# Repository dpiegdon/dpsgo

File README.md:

<!-- vim: tw=72 fo+=a
-->

DPSGO
=====

David's Pretty Satisfactory Gps-disciplined Oscillator

GPS disciplined oscillator
==========================

Accurate frequency reference for measurement equipment.

A 10MHz OCXO is tuned to a timing signal of a GPS, e.g. the 1PPS output.
A frequency syntheziser then generates different signals from this
reference as needed/configured by the user.

Development status
------------------

Currently I am working on the firmware for V1 of the PCB. During that I
found multiple issues with PCB-V1 (<a
href="https://github.com/dpiegdon/dpsgo/blob/master/pcb/export/PCB-v1.pdf">Schematic</a>)
which hopefully culminate in another revision of the PCB, and then the
firmware. See <a
href="https://github.com/dpiegdon/dpsgo/blob/master/pcb/export/PCB-v1.ERRATA">PCB-V1
ERRATA</a>.

I.e.: usable, but only as a prototype development platform for V2.

The main control loop (OCXO -> frequency comparison -> DAC) works and
the OCXO can be tuned to the GPS signal within 1PPB or better.

The chosen *tiny* FPGA is too small to hold all the logic that was
designated for it. Most LEDs are connected to it and cannot be addressed
because of that. Currently also the rotary encoder and buttons are
connected to it and are usable, but may be removed to have more logic
for frequency adjustment. In PCB-V2 I will likely move the UI to the
microcontroller, or pick a slightly larger FPGA, e.g. the HX1K.

System components PCB-V1
------------------------

<a
href="https://github.com/dpiegdon/dpsgo/blob/master/pcb/export/PCB-v1.pdf">Schematic.</a>

OCXO: refurbished 8663-XS with 10MHz output

DAC: AD5761R 16bit high quality low speed DAC with internal reference,
generates tuning signal for OCXO

GPS: uBlox NEO 7M module with 1PPS output

VCXO: Si5351-C frequency generator for programmable output frequencies

 * CLK0: 90MHz as input for frequency comparison in the FPGA (for
   automatic tuning)

 * CLK1: 10MHz reference output signal

 * other programmable outputs (currently disabled)

FPGA: Lattice LP384: measures difference between the generated reference
output and the GPS reference signal. That information is used to
calculate the tuning voltage for the OCXO.

uC: nRF52840 as system- and display-controller

Power input: 14-16V

PMIC: TPS652510 PMIC generating three rails of:

 * 12V: OCXO

 * 3.3V: digital logic

 * 1.2V: FPGA core voltage

Additional LDO for:

 * 10V: DAC output rail (from 12V rail)

Temperature sensors: MCP9808 under OCXO and on bottom-side of PMIC (not
visible in photo).

User interface:

 * SSD1306

 * Rotary encoder and buttons (via FPGA)

 * LEDs (currently not addressalbe as FPGA cannot hold more logic)

Interfaces:

 * USB to both GPS receiver and microcontroller

 * potentially Bluetooth or 802.11.5 to microcontroller

 * JTAG/SWD to microcontroller

External references
-------------------

A list of some hobby GPSDO designs:
https://attila.kinali.ch/blog/2016/02/07/gps-disciplined-oscillator

A GPSDO with rubidium standard:
http://www.medpants.com/my-reeds/itemlist/category/28-electronics

Alternative OCXO tuning schematic:
https://gerrysweeney.com/wp-content/uploads/2013/10/OCXO-Rev-1F.png

"bt7tbl" GPSDO that can be bought on the internets:
https://www.eevblog.com/forum/testgear/bg7tbl-gpsdo-master-reference/

Single-chip GPSDO control loop GPSDO:
https://www.analog.com/media/en/technical-documentation/application-notes/AN-1002.pdf

"OpenPPS" GPSDO project:
http://www.rocketmanrc.com/openpps.html

"Themis" GPSDO from HPSDR:
http://openhpsdr.org/wiki/index.php?title=GPSTCXO

GPSDO by dfannin:
https://github.com/dfannin/gpsdo

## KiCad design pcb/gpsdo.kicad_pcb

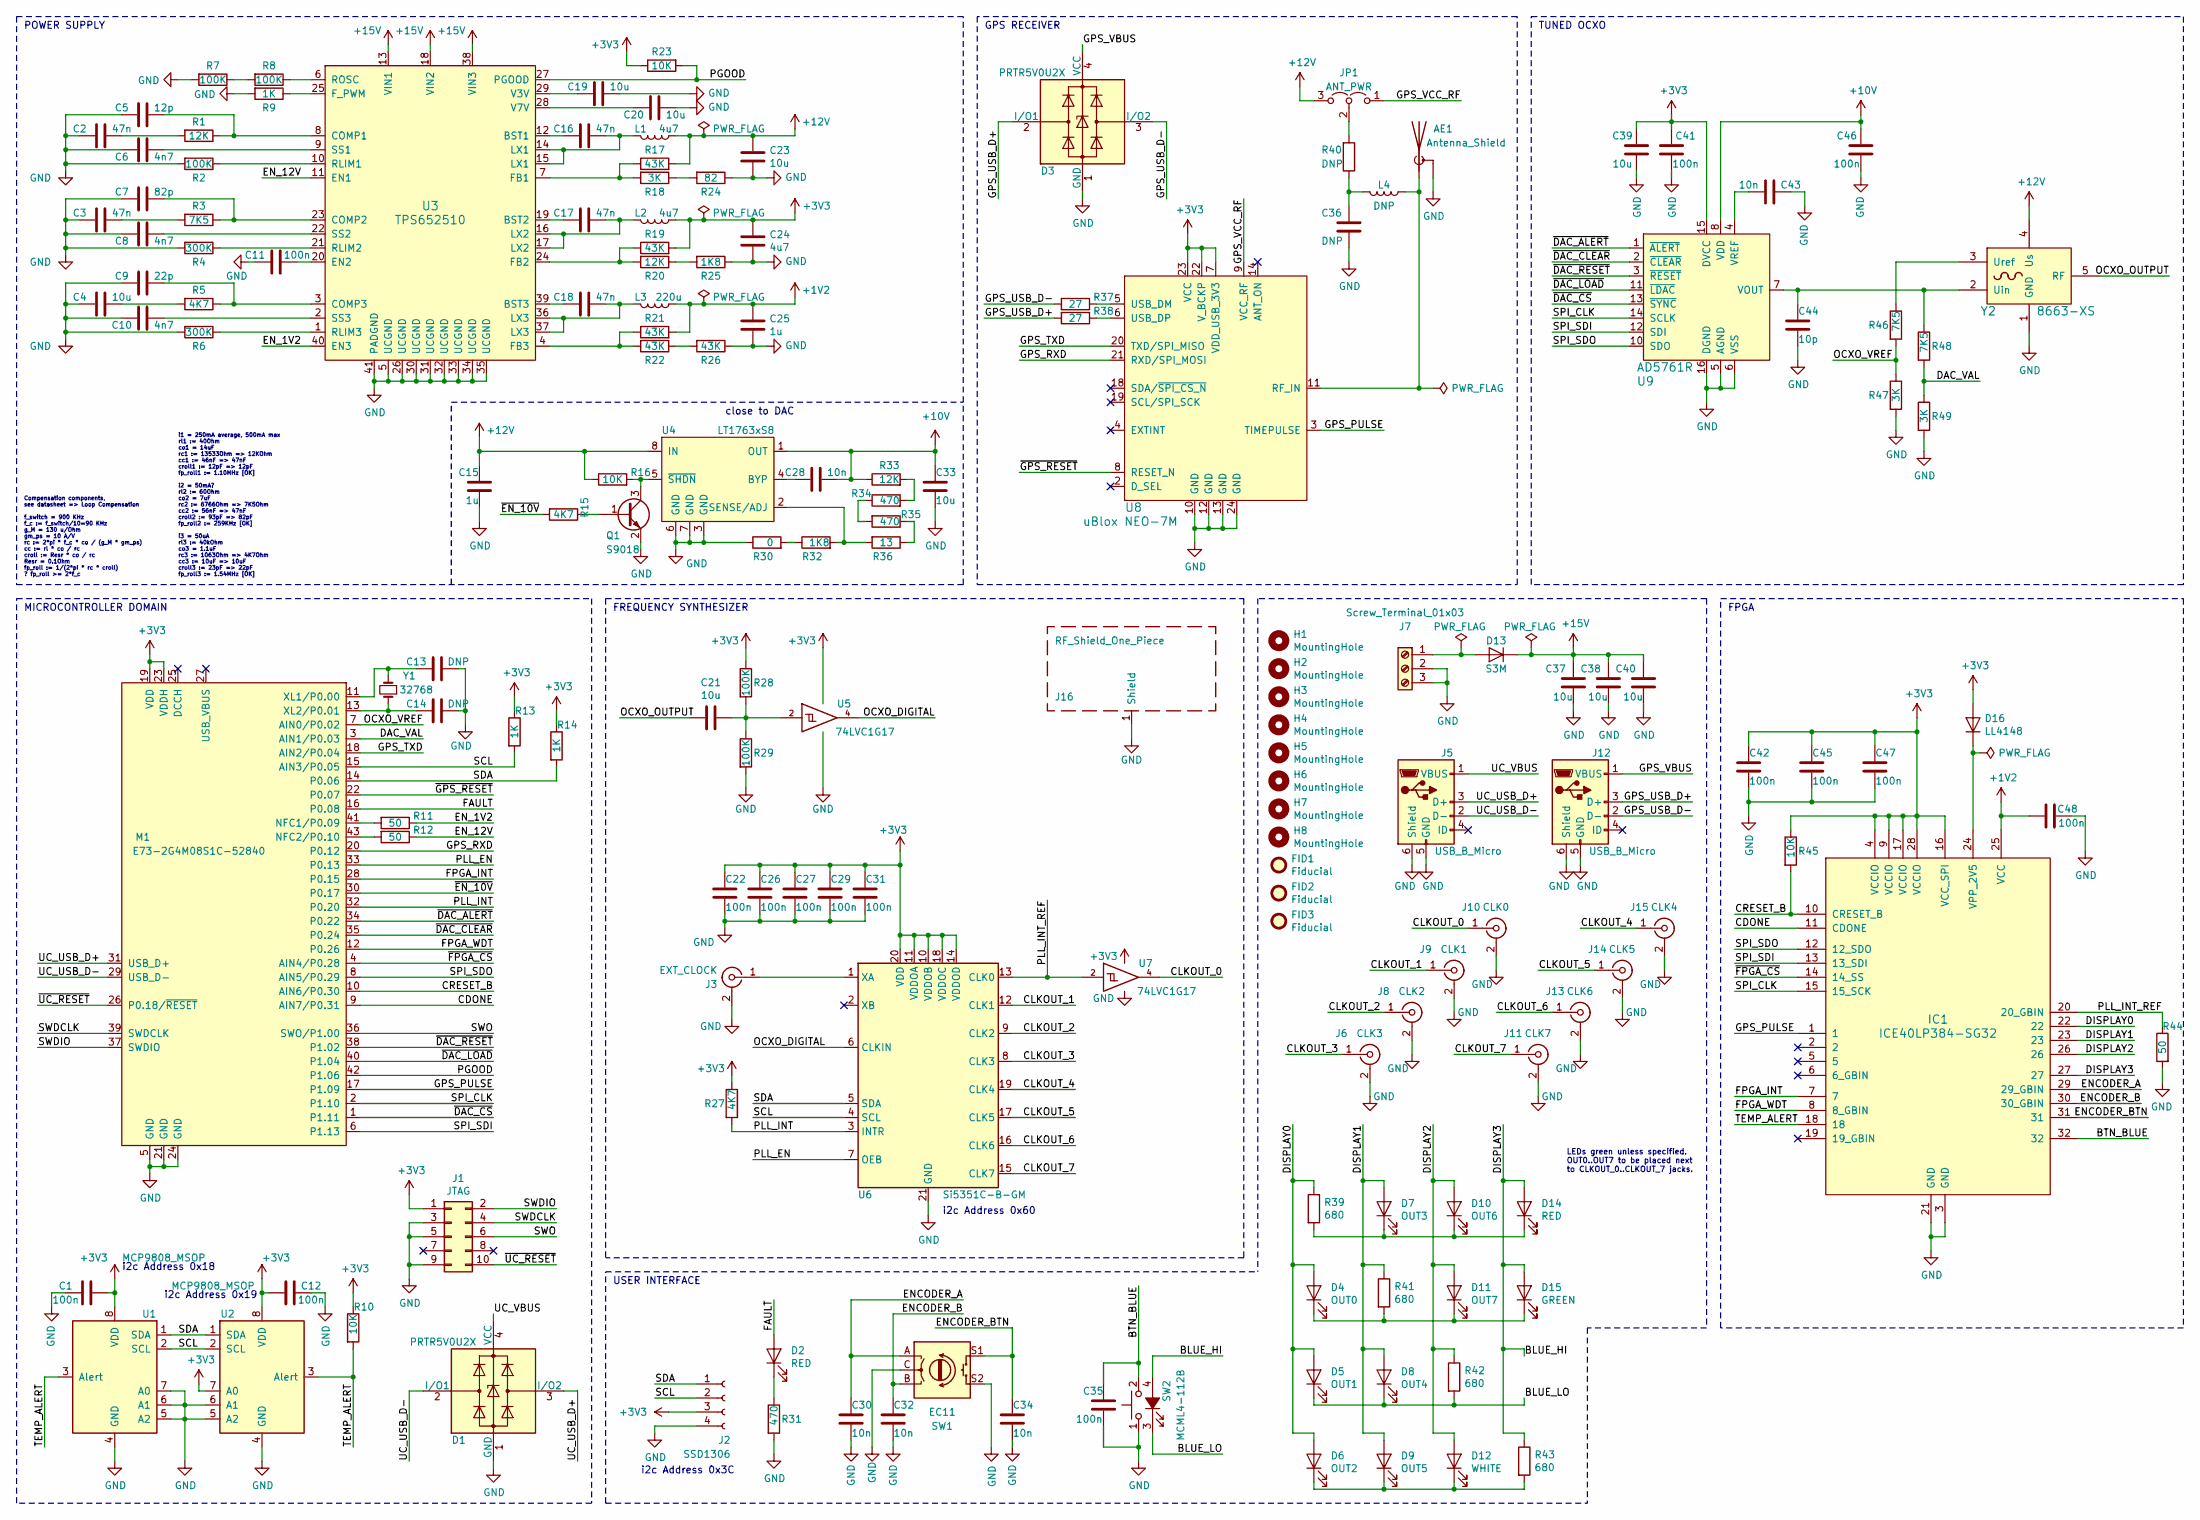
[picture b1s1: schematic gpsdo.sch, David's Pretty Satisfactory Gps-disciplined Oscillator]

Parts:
AE1: Antenna_Shield; Antenna-GPS-1575R
C1, C11, C12, C22, C26, C27, C29, C31, C35, C41, C42, C45, C46, C47, C48: 100n; C_0402_1005Metric
C2, C3, C16, C17, C18: 47n; C_0402_1005Metric
C4: 10u; C_0402_1005Metric
C5: 12p; C_0402_1005Metric
C6, C8, C10: 4n7; C_0402_1005Metric
C7: 82p; C_0402_1005Metric
C9: 22p; C_0402_1005Metric
C13, C14, C36: DNP; C_0402_1005Metric
C15, C25: 1u; C_0603_1608Metric
C19, C20, C33, C39: 10u; C_0603_1608Metric
C21, C23, C37, C38, C40: 10u; C_1210_3225Metric
C24: 4u7; C_0603_1608Metric
C28, C30, C32, C34, C43: 10n; C_0402_1005Metric
C44: 10p; C_0402_1005Metric
D1, D3: PRTR5V0U2X; SOT-143
D2: RED; D_1206_3216Metric
D4: OUT0; D_0603_1608Metric
D5: OUT1; D_0603_1608Metric
D6: OUT2; D_0603_1608Metric
D7: OUT3; D_0603_1608Metric
D8: OUT4; D_0603_1608Metric
D9: OUT5; D_0603_1608Metric
D10: OUT6; D_0603_1608Metric
D11: OUT7; D_0603_1608Metric
D12: WHITE; D_0603_1608Metric
D13: S3M; D_2010_5025Metric
D14: RED; D_0603_1608Metric
D15: GREEN; D_0603_1608Metric
D16: LL4148; D_MiniMELF
FID1, FID2, FID3: Fiducial; Fiducial_1mm_Mask3mm
H1, H2, H3, H4, H5, H6, H7, H8: MountingHole; MountingHole_4.3mm_M4_ISO14580_Pad
IC1: ICE40LP384-SG32; QFN-32-1EP_5x5mm_P0.5mm_EP3.6x3.6mm
J1: JTAG; PinHeader_2x05_P1.27mm_Vertical_SMD
J2: SSD1306; PinHeader_1x04_P2.54mm_Vertical
J3: EXT_CLOCK; U.FL_Molex_MCRF_73412-0110_Vertical
J5, J12: USB_B_Micro; USB_Micro-B_Aliexpress_7.2mm_Pitch
J6: CLK3; SMA_Molex_73251-1153_EdgeMount_Horizontal
J7: Screw_Terminal_01x03; TerminalBlock_Phoenix_PT-1,5-3-5.0-H_1x03_P5.00mm_Horizontal
J8: CLK2; SMA_Molex_73251-1153_EdgeMount_Horizontal
J9: CLK1; SMA_Molex_73251-1153_EdgeMount_Horizontal
J10: CLK0; SMA_Molex_73251-1153_EdgeMount_Horizontal
J11: CLK7; SMA_Molex_73251-1153_EdgeMount_Horizontal
J13: CLK6; SMA_Molex_73251-1153_EdgeMount_Horizontal
J14: CLK5; SMA_Molex_73251-1153_EdgeMount_Horizontal
J15: CLK4; SMA_Molex_73251-1153_EdgeMount_Horizontal
J16: RF_Shield_One_Piece; Laird_Technologies_BMI-S-202-F_16.50x16.50mm
JP1: ANT_PWR; SolderJumper-3_P1.3mm_Open_RoundedPad1.0x1.5mm
L1, L2: 4u7; L_7.3x7.3_H4.5
L3: 220u; L_Vishay_IHLP-1616
L4: DNP; L_0805_2012Metric
M1: E73-2G4M08S1C-52840; E73-2G4M80S1C
Q1: S9018; SOT-23
R1, R20: 12K; R_0402_1005Metric
R2, R7, R8, R28, R29: 100K; R_0402_1005Metric
R3: 7K5; R_0402_1005Metric
R4, R6: 300K; R_0402_1005Metric
R5, R27: 4K7; R_0402_1005Metric
R9, R13, R14: 1K; R_0402_1005Metric
R10, R23, R45: 10K; R_0402_1005Metric
R11, R12, R44: 50; R_0402_1005Metric
R15: 4K7; R_0603_1608Metric
R16: 10K; R_0603_1608Metric
R17: 43K; R_0603_1608Metric
R18, R47, R49: 3K; R_0603_1608Metric
R19, R21, R22, R26: 43K; R_0402_1005Metric
R24: 82; R_0603_1608Metric
R25: 1K8; R_0402_1005Metric
R30: 0; R_0603_1608Metric
R31: 470; R_0402_1005Metric
R32: 1K8; R_0603_1608Metric
R33: 12K; R_0603_1608Metric
R34, R35: 470; R_0603_1608Metric
R36: 13; R_0603_1608Metric
R37, R38: 27; R_0402_1005Metric
R39, R41, R42, R43: 680; R_0402_1005Metric
R40: DNP; R_0402_1005Metric
R46, R48: 7K5; R_0603_1608Metric
SW1: EC11; RotaryEncoder_Alps_EC11E-Switch_Vertical_H20mm
SW2: MCML4-112B; MCML4-L
U1, U2: MCP9808_MSOP; MSOP-8_3x3mm_P0.65mm
U3: TPS652510; QFN-40-1EP_6x6mm_P0.5mm_EP4.6x4.6mm_ThermalVias
U4: LT1763xS8; SO-8_3.9x4.9mm_P1.27mm
U5, U7: 74LVC1G17; SOT-23-5
U6: Si5351C-B-GM; QFN-20-1EP_4x4mm_P0.5mm_EP2.7x2.7mm
U8: uBlox NEO-7M; ublox_NEO_fixed_23
U9: AD5761R; TSSOP-16_4.4x5mm_P0.65mm
Y1: 32768; Crystal_SMD_3215-2Pin_3.2x1.5mm
Y2: 8663-XS; OCXO-8662-8663

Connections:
+1V2: C25.1, C48.1, IC1.25 (VCC), L3.1, R21.2
+3V3: C1.2, C12.2, C22.1, C24.1, C26.1, C27.1, C29.1, C31.1, C39.2, C41.2, C42.1, C45.1, C47.1, D16.2 (A), IC1.4 (VCCIO), IC1.9 (VCCIO), IC1.16 (VCC_SPI), IC1.17 (VCCIO), IC1.28 (VCCIO), J1.1, J2.3, L2.1, M1.19 (VDD), M1.23 (VDDH), R10.1, R13.1, R14.1, R19.2, R23.1, R27.1, R28.1, R45.1, U1.8 (VDD), U2.7 (A0), U2.8 (VDD), U5.5 (VCC), U6.10 (VDDOB), U6.11 (VDDOA), U6.14 (VDDOD), U6.18 (VDDOC), U6.20 (VDD), U7.5 (VCC), U8.7 (VDD_USB_3V3), U8.22 (V_BCKP), U8.23 (VCC), U9.15 (DVCC)
+10V: C28.2, C33.1, C46.2, R33.1, U4.1 (OUT), U9.8 (VDD)
+12V: C15.2, C23.1, JP1.3 (B), L1.1, R16.1, R17.2, U4.8 (IN), Y2.4 (Us)
+15V: C37.2, C38.2, C40.2, D13.1 (K), U3.13 (VIN1), U3.18 (VIN2), U3.38 (VIN3)
/BLUE_HI: D14.2 (A), D15.2 (A), IC1.27, R43.1, SW2.4 (A)
/BLUE_LO: D5.1 (K), D8.1 (K), R42.2, SW2.3 (K)
/BTN_BLUE: C35.1, IC1.32, SW2.2
/CDONE: IC1.11 (CDONE), M1.9 (AIN7/P0.31)
/CLKOUT_0: J10.1 (In), U7.4
/CLKOUT_1: J9.1 (In), U6.12 (CLK1)
/CLKOUT_2: J8.1 (In), U6.9 (CLK2)
/CLKOUT_3: J6.1 (In), U6.8 (CLK3)
/CLKOUT_4: J15.1 (In), U6.19 (CLK4)
/CLKOUT_5: J14.1 (In), U6.17 (CLK5)
/CLKOUT_6: J13.1 (In), U6.16 (CLK6)
/CLKOUT_7: J11.1 (In), U6.15 (CLK7)
/CRESET_B: IC1.10 (CRESET_B), M1.10 (AIN6/P0.30), R45.2
/DAC_VAL: M1.3 (AIN1/P0.03), R48.2, R49.1
/DISPLAY0: D4.2 (A), D5.2 (A), D6.2 (A), IC1.22, R39.1
/DISPLAY1: D7.2 (A), D8.2 (A), D9.2 (A), IC1.23, R41.1
/DISPLAY2: D10.2 (A), D11.2 (A), D12.2 (A), IC1.26, R42.1
/ENCODER_A: C30.1, IC1.29 (29_GBIN), SW1.A
/ENCODER_B: C32.1, IC1.30 (30_GBIN), SW1.B
/ENCODER_BTN: C34.1, IC1.31, SW1.S1
/EN_1V2: R11.1, U3.40 (EN3)
/EN_12V: R12.1, U3.11 (EN1)
/FAULT: D2.2 (A), M1.16 (P0.08)
/FPGA_INT: IC1.7, M1.28 (P0.15)
/FPGA_WDT: IC1.8 (8_GBIN), M1.12 (P0.26)
/GPS_PULSE: IC1.1, M1.17 (P1.09), U8.3 (TIMEPULSE)
/GPS_RXD: M1.20 (P0.12), U8.21 (RXD/SPI_MOSI)
/GPS_TXD: M1.18 (AIN2/P0.04), U8.20 (TXD/SPI_MISO)
/GPS_USB_D+: D3.2 (I/O1), J12.3 (D+), R38.2
/GPS_USB_D-: D3.3 (I/O2), J12.2 (D-), R37.2
/GPS_VBUS: D3.4 (VCC), J12.1 (VBUS)
/GPS_VCC_RF: JP1.1 (A), U8.9 (VCC_RF)
/OCXO_DIGITAL: U5.4, U6.6 (CLKIN)
/OCXO_OUTPUT: C21.2, Y2.5 (RF)
/OCXO_VREF: M1.7 (AIN0/P0.02), R46.2, R47.1
/PGOOD: M1.42 (P1.06), R23.2, U3.27 (PGOOD)
/PLL_EN: M1.33 (P0.13), U6.7 (OEB)
/PLL_INT: M1.32 (P0.20), R27.2, U6.3 (INTR)
/PLL_INT_REF: IC1.20 (20_GBIN), R44.1, U6.13 (CLK0), U7.2
/SCL: J2.2, M1.15 (AIN3/P0.05), R13.2, U1.2 (SCL), U2.2 (SCL), U6.4 (SCL)
/SDA: J2.1, M1.14 (P0.06), R14.2, U1.1 (SDA), U2.1 (SDA), U6.5 (SDA)
/SPI_CLK: IC1.15 (15_SCK), M1.2 (P1.10), U9.14 (SCLK)
/SPI_SDI: IC1.13 (13_SDI), M1.6 (P1.13), U9.12 (SDI)
/SPI_SDO: IC1.12 (12_SDO), M1.8 (AIN5/P0.29), U9.10 (SDO)
/SWDCLK: J1.4, M1.39 (SWDCLK)
/SWDIO: J1.2, M1.37 (SWDIO)
/SWO: J1.6, M1.36 (SWO/P1.00)
/TEMP_ALERT: IC1.18, R10.2, U1.3 (Alert), U2.3 (Alert)
/UC_USB_D+: D1.3 (I/O2), J5.3 (D+), M1.31 (USB_D+)
/UC_USB_D-: D1.2 (I/O1), J5.2 (D-), M1.29 (USB_D-)
/UC_VBUS: D1.4 (VCC), J5.1 (VBUS)
/~DAC_ALERT: M1.34 (P0.22), U9.1 (~ALERT)
/~DAC_CLEAR: M1.35 (P0.24), U9.2 (~CLEAR)
/~DAC_CS: M1.1 (P1.11), U9.13 (~SYNC)
/~DAC_LOAD: M1.40 (P1.04), U9.11 (~LDAC)
/~DAC_RESET: M1.38 (P1.02), U9.3 (~RESET)
/~EN_10V: M1.30 (P0.17), R15.2
/~FPGA_CS: IC1.14 (14_SS), M1.4 (AIN4/P0.28)
/~GPS_RESET: M1.22 (P0.07), U8.8 (RESET_N)
/~UC_RESET: J1.10, M1.26 (P0.18/~RESET)
GND: AE1.2 (Shield), C1.1, C2.2, C3.2, C4.2, C5.1, C6.1, C7.1, C8.1, C9.1, C10.1, C11.1, C12.1, C13.1, C14.1, C15.1, C19.1, C20.1, C22.2, C23.2, C24.2, C25.2, C26.2, C27.2, C29.2, C30.2, C31.2, C32.2, C33.2, C34.2, C35.2, C36.2, C37.1, C38.1, C39.1, C40.1, C41.1, C42.2, C43.2, C44.2, C45.2, C46.1, C47.2, C48.2, D1.1 (GND), D3.1 (GND), IC1.3 (GND), IC1.21 (GND), J1.3, J1.5, J1.9, J2.4, J3.2 (Ext), J5.5 (GND), J5.6 (Shield), J6.2 (Ext), J7.2, J7.3, J8.2 (Ext), J9.2 (Ext), J10.2 (Ext), J11.2 (Ext), J12.5 (GND), J12.6 (Shield), J13.2 (Ext), J14.2 (Ext), J15.2 (Ext), J16.1, M1.5 (GND), M1.21 (GND), M1.24 (GND), Q1.2 (E), R2.2, R4.2, R6.2, R7.2, R9.2, R24.1, R25.1, R26.1, R29.2, R30.1, R31.2, R44.2, R47.2, R49.2, SW1.C, SW1.S2, SW2.1, U1.4 (GND), U1.5 (A2), U1.6 (A1), U1.7 (A0), U2.4 (GND), U2.5 (A2), U2.6 (A1), U3.5 (UCGND), U3.26 (UCGND), U3.30 (UCGND), U3.31 (UCGND), U3.32 (UCGND), U3.33 (UCGND), U3.34 (UCGND), U3.35 (UCGND), U3.41 (PADGND), U4.3 (GND), U4.6 (GND), U4.7 (GND), U5.3 (GND), U6.21 (GND), U7.3 (GND), U8.10 (GND), U8.12 (GND), U8.13 (GND), U8.24 (GND), U9.5 (AGND), U9.6 (VSS), U9.16 (DGND), Y2.1 (GND)
unnamed: AE1.1 (A), L4.1, U8.11 (RF_IN)
unnamed: C2.1, R1.2
unnamed: C3.1, R3.2
unnamed: C4.1, R5.2
unnamed: C5.2, R1.1, U3.8 (COMP1)
unnamed: C6.2, U3.9 (SS1)
unnamed: C7.2, R3.1, U3.23 (COMP2)
unnamed: C8.2, U3.22 (SS2)
unnamed: C9.2, R5.1, U3.3 (COMP3)
unnamed: C10.2, U3.2 (SS3)
unnamed: C11.2, U3.20 (EN2)
unnamed: C13.2, M1.11 (XL1/P0.00), Y1.2
unnamed: C14.2, M1.13 (XL2/P0.01), Y1.1
unnamed: C16.1, L1.2, U3.14 (LX1), U3.15 (LX1)
unnamed: C16.2, U3.12 (BST1)
unnamed: C17.1, L2.2, U3.16 (LX2), U3.17 (LX2)
unnamed: C17.2, U3.19 (BST2)
unnamed: C18.1, L3.2, U3.36 (LX3), U3.37 (LX3)
unnamed: C18.2, U3.39 (BST3)
unnamed: C19.2, U3.29 (V3V)
unnamed: C20.2, U3.28 (V7V)
unnamed: C21.1, R28.2, R29.1, U5.2
unnamed: C28.1, U4.4 (BYP)
unnamed: C36.1, L4.2, R40.1
unnamed: C43.1, U9.4 (VREF)
unnamed: C44.1, R48.1, U9.7 (VOUT), Y2.2 (Uin)
unnamed: D2.1 (K), R31.1
unnamed: D7.1 (K), D10.1 (K), D14.1 (K), R39.2
unnamed: D4.1 (K), D11.1 (K), D15.1 (K), R41.2
unnamed: D6.1 (K), D9.1 (K), D12.1 (K), R43.2
unnamed: D13.2 (A), J7.1
unnamed: D16.1 (K), IC1.24 (VPP_2V5)
unnamed: J3.1 (In), U6.1 (XA)
unnamed: JP1.2 (C), R40.2
unnamed: M1.41 (NFC1/P0.09), R11.2
unnamed: M1.43 (NFC2/P0.10), R12.2
unnamed: Q1.1 (B), R15.1
unnamed: Q1.3 (C), R16.2, U4.5 (~SHDN)
unnamed: R2.1, U3.10 (RLIM1)
unnamed: R4.1, U3.21 (RLIM2)
unnamed: R6.1, U3.1 (RLIM3)
unnamed: R7.1, R8.2
unnamed: R8.1, U3.6 (ROSC)
unnamed: R9.1, U3.25 (F_PWM)
unnamed: R17.1, R18.2, U3.7 (FB1)
unnamed: R18.1, R24.2
unnamed: R19.1, R20.2, U3.24 (FB2)
unnamed: R20.1, R25.2
unnamed: R21.1, R22.2, U3.4 (FB3)
unnamed: R22.1, R26.2
unnamed: R30.2, R32.1
unnamed: R32.2, R36.2, U4.2 (SENSE/ADJ)
unnamed: R33.2, R34.2
unnamed: R34.1, R35.2
unnamed: R35.1, R36.1
unnamed: R37.1, U8.5 (USB_DM)
unnamed: R38.1, U8.6 (USB_DP)
unnamed: R46.1, Y2.3 (Uref)

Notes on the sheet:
POWER SUPPLY
GPS RECEIVER
MICROCONTROLLER DOMAIN
TUNED OCXO
FREQUENCY SYNTHESIZER
FPGA
USER INTERFACE
close to DAC
i1 = 250mA average, 500mA max rl1 := 40Ohm co1 = 14uF rc1 := 13533Ohm => 12KOhm cc1 := 46nF => 47nF croll1 := 12pF => 12pF fp_roll1 := 1.10MHz [OK] i2 = 50mA? rl2 := 60Ohm co2 = 7uF rc2 := 6766Ohm => 7K5Ohm cc2 := 56nF => 47nF croll2 := 93pF => 82pF fp_roll2 := 259KHz [OK] i3 = 50uA rl3 := 40kOhm c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
Compensation components, see datasheet => Loop Compensation f_switch = 900 KHz f_c := f_switch/10=90 KHz g_M = 130 u/Ohm gm_ps = 10 A/V rc := 2*pi * f_c * co / (g_M * gm_ps) cc := rl * co / rc croll := Resr * co / rc Resr = 0.1Ohm fp_roll := 1/(2*pi * rc * croll) ? fp_roll >= 2*f_c
LEDs green unless specified. OUT0..OUT7 to be placed next to CLKOUT_0..CLKOUT_7 jacks.
i2c Address 0x19
i2c Address 0x3C
i2c Address 0x60
i2c Address 0x18

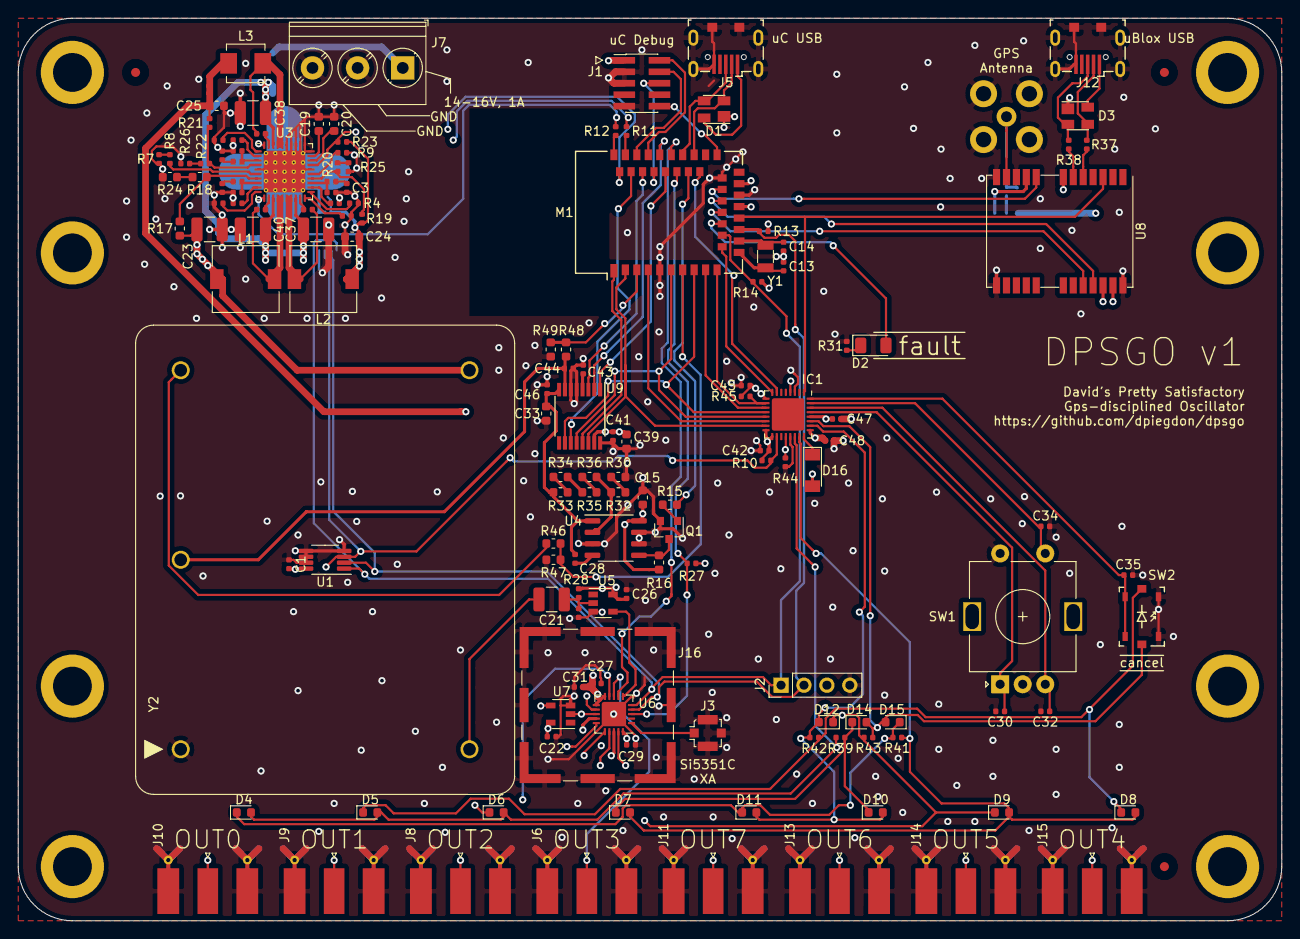
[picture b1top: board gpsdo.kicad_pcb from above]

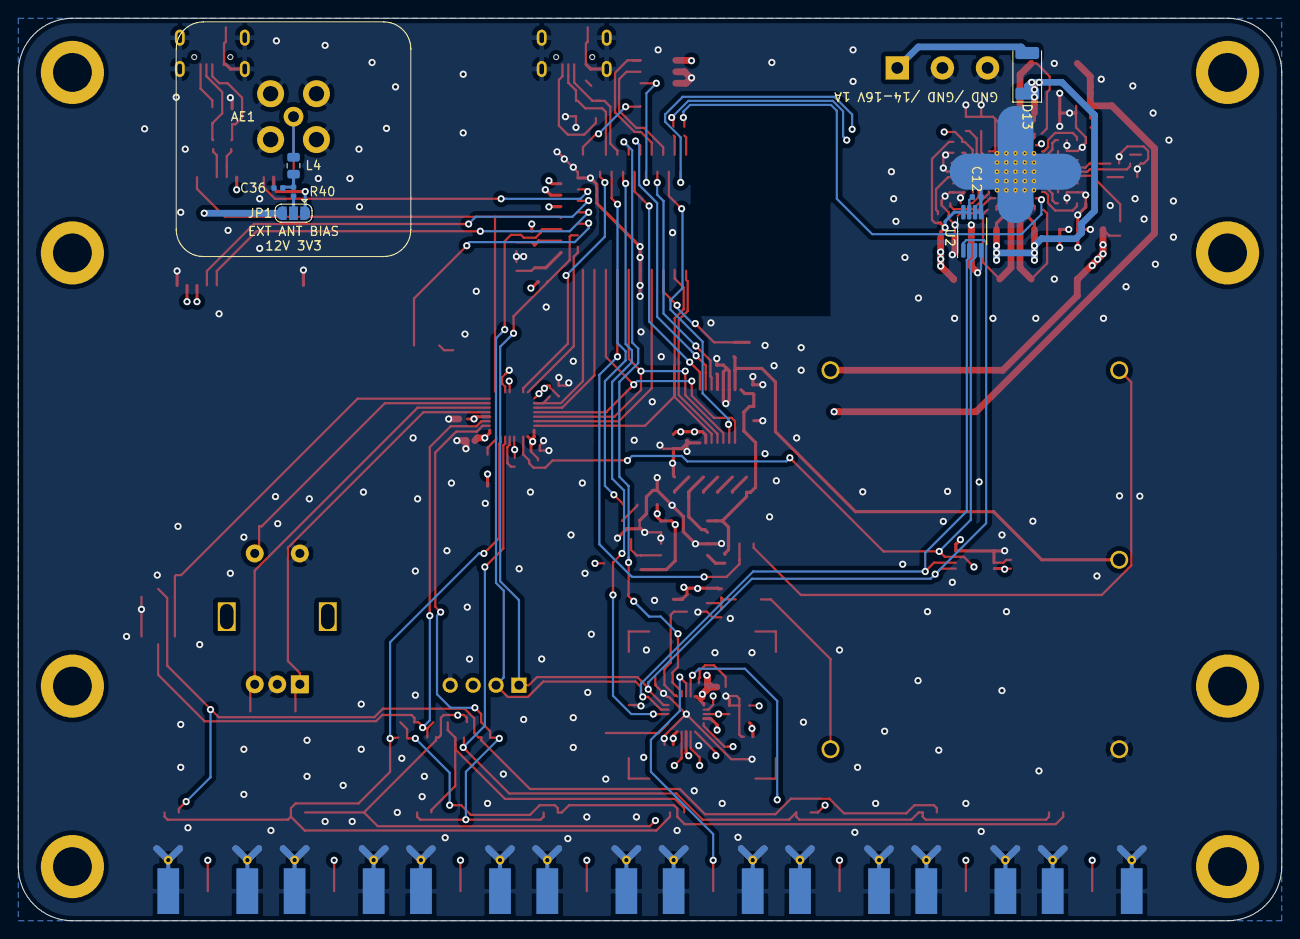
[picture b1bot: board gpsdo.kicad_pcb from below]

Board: 4 copper layers, 140.0 x 100.0 mm, 161 parts (8 on the bottom side), 124 nets.

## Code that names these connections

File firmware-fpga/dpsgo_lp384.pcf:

# SPI interface
set_io --warn-no-port SCK 15
set_io --warn-no-port SS 14
set_io --warn-no-port SDI 13
set_io --warn-no-port SDO 12
set_io --warn-no-port FPGA_INT 7
set_io --warn-no-port FPGA_WDT 8

# clocks
set_io --warn-no-port MAJOR_CLOCK 20
set_io --warn-no-port MINOR_CLOCK 1

# other IO
set_io --warn-no-port TEMP_ALERT 18

# buttons and encoder
set_io --warn-no-port ENCODER_A 29
set_io --warn-no-port ENCODER_B 30
set_io --warn-no-port ENCODER_BTN 31
set_io --warn-no-port BTN_BLUE 32

# LED matrix
set_io --warn-no-port LED_MATRIX[0] 22
set_io --warn-no-port LED_MATRIX[1] 23
set_io --warn-no-port LED_MATRIX[2] 26
set_io --warn-no-port LED_MATRIX[3] 27

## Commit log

2020-04-05 ignore temporary/intermediate files
2020-04-05 stub PCB files
2020-04-05 add submodules
2020-04-05 concept PCB
2020-04-05 description / concept
2020-04-05 add 8663-XS OCXO
2020-04-05 add ublox NEO-7 GPS module
2020-04-05 schematic progress, mark areas with TODOs
2020-04-06 add TPS652510, schematic progress and layout
2020-04-06 PCB progress
2020-04-06 schematic progress
2020-04-08 UI: rotary encoder would be nice, cleanup
2020-04-08 remove some errors and warnings
2020-04-08 project name: DPSGO; update README
2020-04-09 power concepts; bias and digitze OCXO output
2020-04-10 power progress, cleanup
2020-04-10 LEDs, front/rear panel
2020-04-11 stub verilog implementation to see how much logic fits into the LP384 ; schematic adaptions for that
2020-04-11 FPGA progress, interface and schematic-cleanup
2020-04-11 partial footprint assignment
2020-04-12 footprints, GPS antenna optionally can be biased now
2020-04-12 cleanup
2020-04-12 review progress of schematic
2020-04-13 review footprints and more
2020-04-13 add current netlist
2020-04-13 first routing tests
2020-04-13 replace expensive Si7010 with two cheaper temp sensors
2020-04-13 remove PCB routing, restart from scratch
2020-04-14 new routing
2020-04-15 tps652510 routing, inductor footprint
2020-04-16 tps652510 routing
2020-04-16 basic component placement and board layout
2020-04-17 pin assignment optimization, routing
2020-04-17 routing progress, silkscreen
2020-04-17 more layout cleanup
2020-04-17 add mounting holes, cleanup bord edge and mounting strategy. increase board size for that.
2020-04-17 added shield and more silkscreen, cleanup
2020-04-18 more routing cleanup
2020-04-18 PCB v1
    more cleanup, release v1
2020-04-18 adapt FPGA pinout to PCB-v1
2020-04-18 add temp-alert to interrupt register
2020-04-18 add schematic to PCB-v1 exports
2020-04-18 add notes on PCB-v1 improvements
2020-04-20 fix missing PAD23 of ublox neo in paste layer (thanks to JLCPCB for spotting this!)
2020-04-22 add errata note on ublox pad 23
2020-04-25 implement encoder, latch UIO only on rising edge.
    user IO output is generated with slower clock. so only latch them on
    rising edge.
2020-04-25 split encoder into generics and platform-specific pull-up
2020-04-30 add PCB V1 errata on power rail ripple
2020-04-30 fix L3 to decrease ripple on 1V2 rail
2020-05-01 added more ERRATA for the PCB
2020-05-02 more errata for PCB
2020-05-02 strip firmware dir, will be pulled in as extra submodule
2020-05-03 add microcontroller firmware
2020-05-03 latest firmware stub
2020-05-05 more PCB-v1 errata
2020-05-07 change GPS antenna to support either ceramic antenna or SMA with optional bias
2020-05-07 increase distance between input protection diode and GND pin of input connector
2020-05-07 increase distance of DAC output rail to any noisy digital signal
2020-05-07 increase visibility of pin1 of SWD connector.
2020-05-21 add errata on R44 overloading CLK0 output with 50Ohm. reduce to 470Ohm
2020-05-22 current firmware status
2020-05-25 more errata notes
2020-05-25 current firmware state
2020-05-28 use sensible display clock, default-on all LEDS for visual check
2020-05-28 firmware tests
2020-05-28 use SPI mode 1 for FPGA, trigger UIO on button-press, not on button release
2020-05-30 PCB errata & documentation
2020-05-30 fix rotary encoder, disable debouncing, use improved display
2020-05-30 fix logic error that lead to GPS-clock not being tracked.
    also 35% of logic was missing due to this. so now we have a
    size-problem. we'll have to remove features and move e.g. the display
    and maybe the controls into the microcontroller in the next revision.
    too bad, I really liked the idea.
2020-05-30 strip down FPGA design to fit into LP384: remove LEDs
2020-05-30 optimize FPGA timings and include temperature alert as input.
2020-05-30 basic firmware
2020-05-30 more PCB errata
2020-06-05 logic reduction in FPGA
2020-06-05 current state + some documentation for public release
2020-06-05 add script to calculate improved values for power supply layout of TPS652510
2020-06-05 minor errata, firmware state
2020-06-06 add schematic links
2020-06-18 improved plotting of fpga schematic
2020-06-18 annotate, add links in documentation
2020-06-19 initial draft for a size-reduced clock comparator
2020-06-19 fix bit-order in spi transfer, some buggy assignments, cleanup
2020-06-19 don't assert interrupts when shifting via SPI.
2020-06-21 use look-ahead in adder/subtractor
2020-06-23 use more look-ahead and proper clock synchronizer
2020-06-23 firmware: adapt to new fpga core
2020-06-23 FPGA: stop downcounting when 0 was reached; add more synchronization buffer
2020-06-23 FPGA: fix bug due to mixup in varname / logic
2020-06-24 firmware with improved control loop
2020-07-15 add notes and latest firmware documentation
2020-07-15 add and cleanup errata
2020-07-23 firmware stuff

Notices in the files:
pcb/gpsdo.kicad_pcb:
(c) 2020 by David R. Piegdon
